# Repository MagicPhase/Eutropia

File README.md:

# Eutropia
Open Source ESP32 Multi Sensor Platform. 

This PCB design offers numerous optional features and configurations built around the ESP-WROOM-32 30PIN module. The footprint is designed to match with the Nextion 2.8" Smart Displays. The primary desgin goal was to have a wide range of sensor inputs coupled with high current outputs to fit an equally wide range of applications. This includes a reasonably small footprint for portability and battery operation.

## Feature list:

- 2 High Power Outputs  
- 2 Optocouple Outputs  
- 2 Medium Power Outputs  
- Current/Voltage sensing  
- RTC Clock  
- Low Pressure Sensor  
- Accelerometer/Gyro  
- Humidity Sensor  
- Water Ingress Sensor  
- 1 Input/Output Port  
- 1 Input Port (multifuntion) 
- 2 Neo Pixel LEDs  
- Mounting Holes For Nextion 2.8" Serial Display

## ESP32 I/O configuration:

>D39(I) Attached to INA3221 programable warning for over current monitor.  
>D36(I) Labelled (AUX1) pin is attached to 3-pin header for general use as default. 
JP3 can connect the MPU (INT) pin for auto calibration. JP1 can connect to water ingress sensor. Only one function can be used.  
>D35(I) Input for thermal sensor near CH2 FET.  
>D34(I) Input for thermal sensor near CH' FET.  
>D33(IO) Output PWM for CH2 FET via driver (MIC4127 CHB).  
>D32(IO) Output PWM for CH1 FET via driver (MIC4127 CHA).  
>D23(IO) Labelled (AUX2) pint is attached to 3-pin JST header for general purpose.  
>D22(IO) I2C SCL pin.  
>D21(IO) I2C SDA pin.  
>D17(IO) Serial TX2 pin.  
>D16(IO) Serial RX2 pin.  
>D19(IO) Output PWM for CH4 FET.  
>D18(IO) Output PWM for CH3 FET.  
>D5(IO) Attached to 2 JTS headers with 4.7k pullup resistor. These are intended for DS18D20 temp sensors.  
>D1(IO) Attached to the input of the Neo Pixel (SK6805). This pin is also used by the Serial port during programing.  
All other IO pins are left unattached as to not interfere during WiFi operations.  

## Board Headers:
>CH1 High Output XT30 Female  
>CH2 High Output XT30 Female  
>CH3 Low Output JST_PH_B2B-PH-K_1x02_P2.00mm  
>CH4 Low Output JST_PH_B2B-PH-K_1x02_P2.00mm  
>HEADER1 I2C PULLUP PinHeader_2x02_P2.00mm  
>HEADER2 VIN/5V SELECT PinHeader_2x03_P2.00mm  
>HEADER3 FET/OPTO SELECT PinHeader_2x03_P2.00mm  
>HEADER4 I2C HEADER	PinHeader_1x04_P2.00mm  
>HEADER5 Serial2  PinHeader_1x04_P2.50mm  

Two High Power FET's capable of >50watt output. These channels have current/voltage monitoring, thermal monitoring, and safety fuses. These outputs are selectable with two optocoupler drivers via a jumper header.
  
Two Medium power FET's capable of 10watt output. These channels Have selectable input voltages of either VIN(12-24) or 5V.
  
Three channels of current/voltage monitoring. Monitoring is split between the 2 high current channels and the remainder of all devices on the board. Total power usage is a sum of all three channels.
  
RTC clock is used for basic time keeping and has battery backup.
  
The low pressure sensor is an absolute pressure type and designed for low pressure monitoring of <10psi. The sensor has a metal port.
  
Accelerometer/gyro optional port is compatible with the MPU-6050 board. It is also possible to fit the MPU-9250, however the board will protrude from the top approximately 5mm and the two lower pins should be clipped. There is also a footprint on the main board for an MPU-6050 chip with selectable I2C address. If the chip is present on the main board, do not populate with an expansion board!
  
One input/output via a three pin JST(2mm pitch) header.
  
One input only pin via a three pin JST(2mm pitch) header. This input is a shared input. See D36 pin configuration.

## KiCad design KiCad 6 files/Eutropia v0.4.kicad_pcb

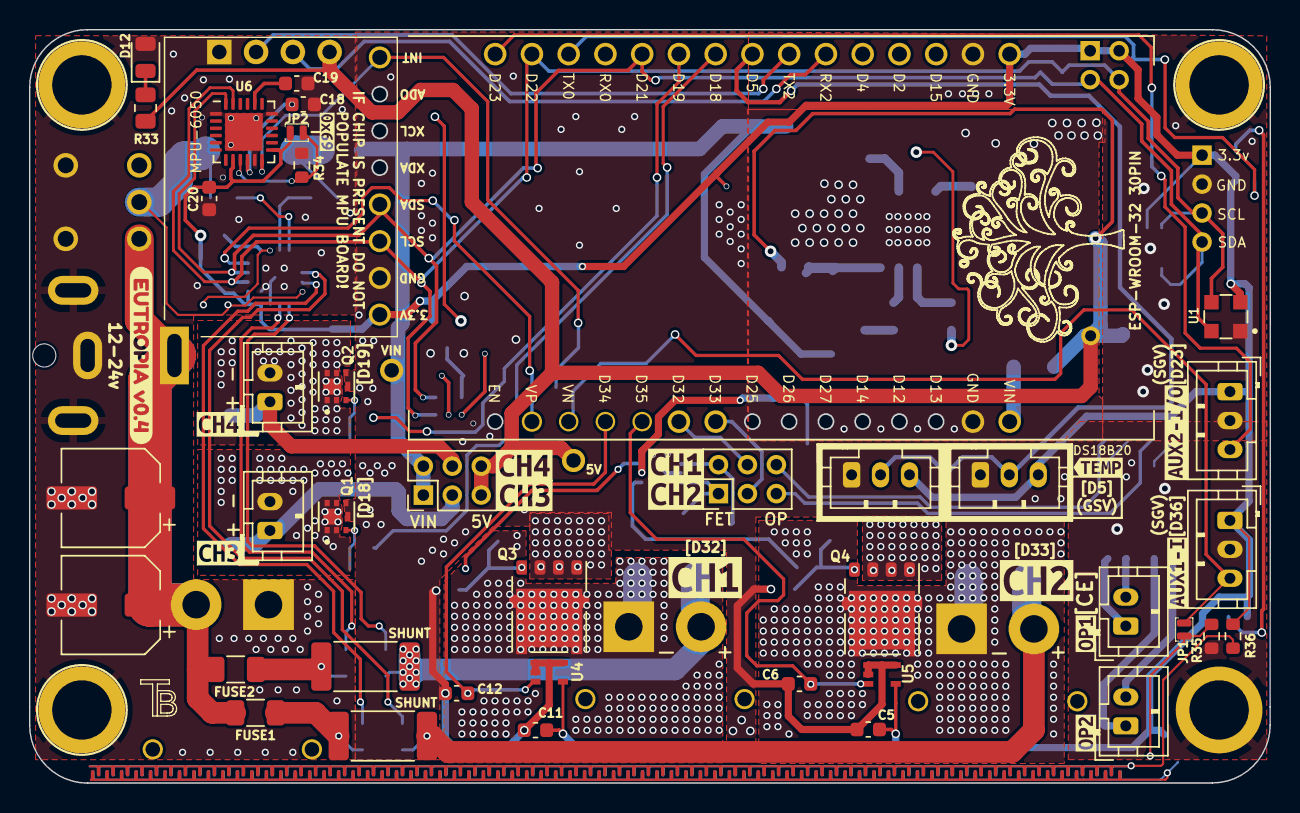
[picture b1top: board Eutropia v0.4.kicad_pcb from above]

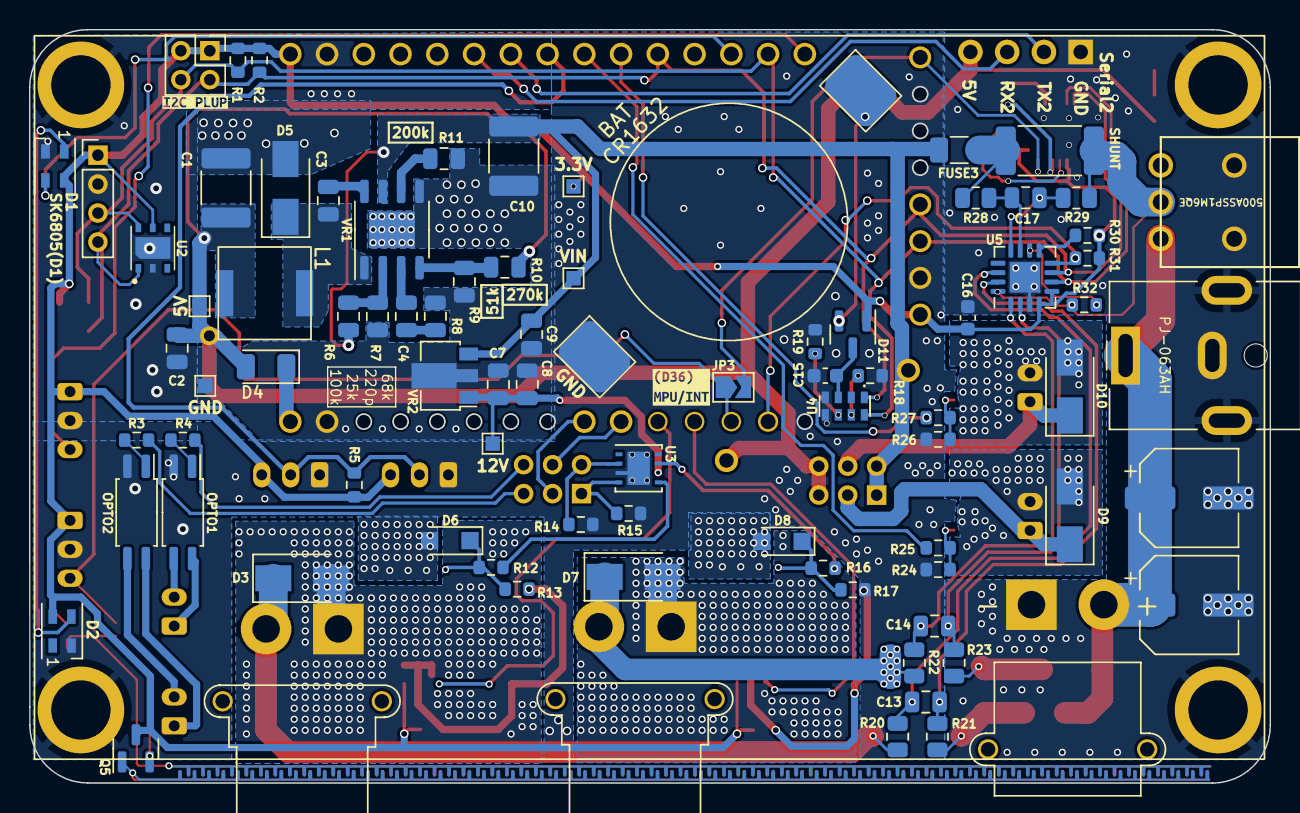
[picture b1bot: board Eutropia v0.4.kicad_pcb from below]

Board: 2 copper layers, 85.7 x 52.1 mm, 144 parts (88 on the bottom side), 39 nets.

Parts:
BAT: CR1632; CR1632-BU1632SM
BAT1: AMASS_XT30PW-M_1x02_P2.50mm_Horizontal
C1: 22uf; C_1812_4532Metric
C2, C3, C8, C13, C14, C17: .1uf; C_0805_2012Metric
C4: 220pf; C_0805_2012Metric
C5, C11, C15, C16, C18: .1uf; C_0603_1608Metric
C6, C12: 150p; C_0603_1608Metric
C7: 10uf; C_0805_2012Metric
C9: 1uf; C_0805_2012Metric
C10: 10uf; C_1812_4532Metric
C19: 2.2n; C_0603_1608Metric
C20: 10n; C_0603_1608Metric
C21, C22, C23, C24: 100uf; CP_Elec_6.3x7.7
CH1, CH2: AMASS_XT30PW-F_1x02_P2.50mm_Horizontal
CH1(OPTO), CH2(OPTO), CH3, CH4: JST_PH_B2B-PH-K_1x02_P2.00mm_Vertical
D1, D2: SK6805; LED_SK6805_PLCC4_2.4x2.7mm_P1.3mm
D3, D5, D7, D9, D10: CDBA3100-G; D_SMA
D4: SD1206T040S2R0; D_1206_3216Metric
D6, D8: Nexperia_CFP3_SOD-123W
D11: BAS70-05; SOT-23
D12: LED 20ma; LED_0805_2012Metric
ESP-WROOM-32 30PIN: ESP-WROOM-32 30PIN; MODULE_ESP32-DEVKITC-32D V2
FUSE1, FUSE2, FUSE3: Fuse_1206_3216Metric
HEADER1: I2C PULLUP; PinHeader_2x02_P2.00mm_Vertical
HEADER2: VIN/5V SELECT; PinHeader_2x03_P2.00mm_Vertical
HEADER3: FET/OPTO SELECT; PinHeader_2x03_P2.00mm_Vertical
HEADER4: I2C HEADER; PinHeader_1x04_P2.00mm_Vertical
HEADER5: Serial2; PinHeader_1x04_P2.54mm_Horizontal
I/36: JST_PH_B3B-PH-K_1x03_P2.00mm_Vertical
IO/23: JST_PH_B3B-PH-K_1x03_P2.00mm_Vertical
JP1: Water Ingress; Solder Jumper 1mm
JP2: 0x69 MPU I2C; Solder Jumper 1mm
JP3: MPU INT to D36; SolderJumper-2_P1.3mm_Open_TrianglePad1.0x1.5mm
L1: 15uh inductor
MPU: MPU-6050 accelerometer
Nextion 2.8: Nextion 2.8
OPTO1, OPTO2: TCMT1119; SOP-4_4.4x2.6mm_P1.27mm
PJ-063AH: BarrelJack_CUI_PJ-063AH_Horizontal
Q1, Q2: PMPB10XNX; TRANS_PMPB16EPX
Q3, Q4: NTMFS4935NT1G; ONSemi_SO-8FL_488AA
Q5: MMBT2222A; SOT-23
R1, R2, R5: 4.7k; R_0603_1608Metric
R3, R4: 420; R_0603_1608Metric
R6: 100k; C_0805_2012Metric
R7: 25k; C_0805_2012Metric
R8: 68k; C_0805_2012Metric
R9: 51k; C_0805_2012Metric
R10: 270k; C_0805_2012Metric
R11: 200k; C_0805_2012Metric
R12, R16: 50; R_0603_1608Metric
R13, R14, R15, R17, R18, R19, R24, R26, R30, R31, R32, R34, R35: 10k; R_0603_1608Metric
R20, R21, R22, R23, R28, R29: 10; R_0805_2012Metric
R25, R27: 500; R_0603_1608Metric
R33: 150; R_0805_2012Metric
R36: 100; R_0603_1608Metric
SHUNT: 10mohm; R_2512_6332Metric_Pad1.40x3.35mm_HandSolder
SHUNT#2, SHUNT#3: 10mohm; R_2512_6332Metric_Pad1.40x3.35mm_HandSolder
SW1: 500ASSP1M6QE; d22ce012-2fd7-45db-96b5-83cda7ebcca8
TEMP1, TEMP2: JST_PH_B3B-PH-K_1x03_P2.00mm_Vertical
TP1: 5V; Standard Pad TH
TP2: GND; TestPoint_Pad_1.0x1.0mm
TP3: 5V; TestPoint_Pad_1.0x1.0mm
TP4: 12V; TestPoint_Pad_1.0x1.0mm
TP5: VIN; TestPoint_Pad_1.0x1.0mm
TP6: 3.3V; TestPoint_Pad_1.0x1.0mm
U1: MS583702BA01
U2: XDCR_SHT20
U3: MIC4127; MLF-8-1EP_3x3mm_P0.65mm_EP1.55x2.3mm
U4, U5: MAX6613MXK; SC70-5
U4#2: RV-8803
U5#2: INA3221; Texas_RGV_S-PVQFN-N16_EP2.1x2.1mm
U6: MPU-6050; QFN-24-1EP_4x4mm_P0.5mm_EP2.6x2.6mm
VR1: MP1584EN; SOIC-8-1EP_3.9x4.9mm_P1.27mm_EP2.514x3.2mm
VR2: SOT-89-3
kibuzzard-625BD4CB: G***; kibuzzard-625BD4CB
kibuzzard-625BD4D5: G***; kibuzzard-625BD4D5
kibuzzard-625BD9A7: G***; kibuzzard-625BD9A7
kibuzzard-625BD9B1: G***; kibuzzard-625BD9B1
kibuzzard-625BD52D: G***; kibuzzard-625BD52D
kibuzzard-625BD60C: G***; kibuzzard-625BD60C
kibuzzard-625BD91F: G***; kibuzzard-625BD91F
kibuzzard-625BD92B: G***; kibuzzard-625BD92B
kibuzzard-625BD538: G***; kibuzzard-625BD538
kibuzzard-625BD597: G***; kibuzzard-625BD597
kibuzzard-625BDEC7: G***; kibuzzard-625BDEC7
kibuzzard-625BDEDE: G***; kibuzzard-625BDEDE
kibuzzard-625FE1CF: G***; kibuzzard-625FE1CF
kibuzzard-625FE15C: G***; kibuzzard-625FE15C
kibuzzard-625FE593: G***; kibuzzard-625FE593
kibuzzard-6264A044: G***; kibuzzard-6264A044
kibuzzard-62649B95: G***; kibuzzard-62649B95

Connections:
3.3V: C5.2, C11.2, C16.2, C20.2, D1.V, D2.V, D11.A, ESP-WROOM-32 30PIN.3.3V, HEADER1.1, HEADER1.3, HEADER4.1, I/36.1, IO/23.1, JP2.2, MPU.1, Q5.C, R1.1, R2.1, R5.2, R30.1, R31.1, R36.2, TEMP1.3, TEMP2.3, TP6.1, U1.V, U2.VDD, U4.VCC, U5.VCC, U5#2.A0, U5#2.VS, U6.VDD-13, U6.VLOGIC-8
5V: C1.2, C2.2, D4.2, HEADER2.5, HEADER2.6, HEADER5.4, L1.5V, R10.2, R33.2, TP1.1, TP3.1
12V: C7.2, C8.2, TP4.1, U3.Vs, VR2.Vo
BAT: BAT.1, D11.2
CH1+: CH1.2, D7.1, R22.1, SHUNT#2.2
D1: D1.IN, ESP-WROOM-32 30PIN.TX0
D5: ESP-WROOM-32 30PIN.D5, R5.1, TEMP1.2, TEMP2.2
D18: ESP-WROOM-32 30PIN.D18, R25.2
D19: ESP-WROOM-32 30PIN.D19, R27.2
D23: ESP-WROOM-32 30PIN.D23, IO/23.3
D32: ESP-WROOM-32 30PIN.D32, HEADER3.4, HEADER3.6, R4.2, R16.1, U3.OUTA
D33: ESP-WROOM-32 30PIN.D33, HEADER3.3, HEADER3.5, R3.2, R12.1, U3.OUTB
D34: C12.2, ESP-WROOM-32 30PIN.D34(I), U4.OUT
D35: C6.2, ESP-WROOM-32 30PIN.D35(I), U5.OUT
D36: ESP-WROOM-32 30PIN.VN(I), I/36.3, JP1.1, JP3.1, JP3.2, MPU.8, U6.INT-12
D39: ESP-WROOM-32 30PIN.VP(I), R31.2, U5#2.WARN
DRAIN: CH1.1, CH2.1, CH3.2, CH4.2, D3.2, D7.2, D9.2, D10.2, Q1.D, Q2.D, Q3.D, Q4.D
EVI: R18.1, U4#2.EVI
GND: BAT1.1, C1.1, C2.1, C5.1, C6.1, C7.1, C8.1, C9.2, C10.2, C11.1, C12.1, C15.1, C16.1, C18.1, C19.1, C20.1, C21.2, C22.2, C23.2, C24.2, D1.GND, D2.GND, D5.2, D6.2, D8.2, D12.2, ESP-WROOM-32 30PIN.GND, HEADER4.2, HEADER5.1, I/36.2, IO/23.2, MPU.2, Nextion 2.8.1, OPTO1.C, OPTO2.C, PJ-063AH.2, PJ-063AH.MP, Q1.S, Q2.S, Q3.S, Q4.S, R7.2, R8.1, R9.2, R11.2, R13.2, R14.2, R15.2, R17.2, R18.2, R19.1, R24.2, R26.2, R34.2, R35.1, SW1.1, TEMP1.1, TEMP2.1, TP2.1, U1.G, U2.7, U2.GND, U3.GND, U4.G, U4.NC, U4#2.CLKOE, U4#2.Vss, U5.G, U5.NC, U5#2.17, U5#2.GND, U6.25, U6.CLKIN-1, U6.FSYNC-11, U6.GND-18, VR1.5, VR1.9, VR2.G
IN+1: C17.2, R29.2, U5#2.IN+1
IN+2: C13.2, R21.2, U5#2.IN+2
IN+3: C14.2, R23.2, U5#2.IN+3
IN-1: C17.1, R28.2, U5#2.IN-1
IN-2: C13.1, R20.2, U5#2.IN-2
IN-3: C14.1, R22.2, U5#2.IN-3
INA: HEADER3.2, R14.1, U3.INA
INB: HEADER3.1, R15.1, U3.INB
INT: R19.2, U4#2.INT
PV: R32.2, U5#2.PV
RX2: ESP-WROOM-32 30PIN.RX2, HEADER5.3
SCL: ESP-WROOM-32 30PIN.D22 SCL, HEADER1.4, HEADER4.3, MPU.3, R1.2, U1.SCL, U2.SCL, U4#2.SCL, U5#2.SCL, U6.SCL-23
SDA: ESP-WROOM-32 30PIN.D21 SDA, HEADER1.2, HEADER4.4, MPU.4, R2.2, U1.SDA, U2.SDA, U4#2.SDA, U5#2.SDA, U6.SDA-24
SW: C3.2, D5.1, L1.2, VR1.SW
TX2: ESP-WROOM-32 30PIN.TX2, HEADER5.2
VDD: C15.2, D11.C, U4#2.Vdd
VIN: C9.1, C10.1, FUSE3.1, FUSE3.2, HEADER2.1, HEADER2.2, R6.2, R28.1, SHUNT#3.1, TP5.1, VR1.7, VR2.Vi
VIN-NS: BAT1.2, C21.1, C22.1, C23.1, C24.1, FUSE1.1, FUSE2.1, PJ-063AH.1, SW1.2
VPU: R29.1, R32.1, SHUNT#3.2, SW1.3, U5#2.VPU
ch2+: CH2.2, D3.1, R20.1, SHUNT.2

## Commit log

2022-05-04 Rename BOM.html to BOM v0.4.html
